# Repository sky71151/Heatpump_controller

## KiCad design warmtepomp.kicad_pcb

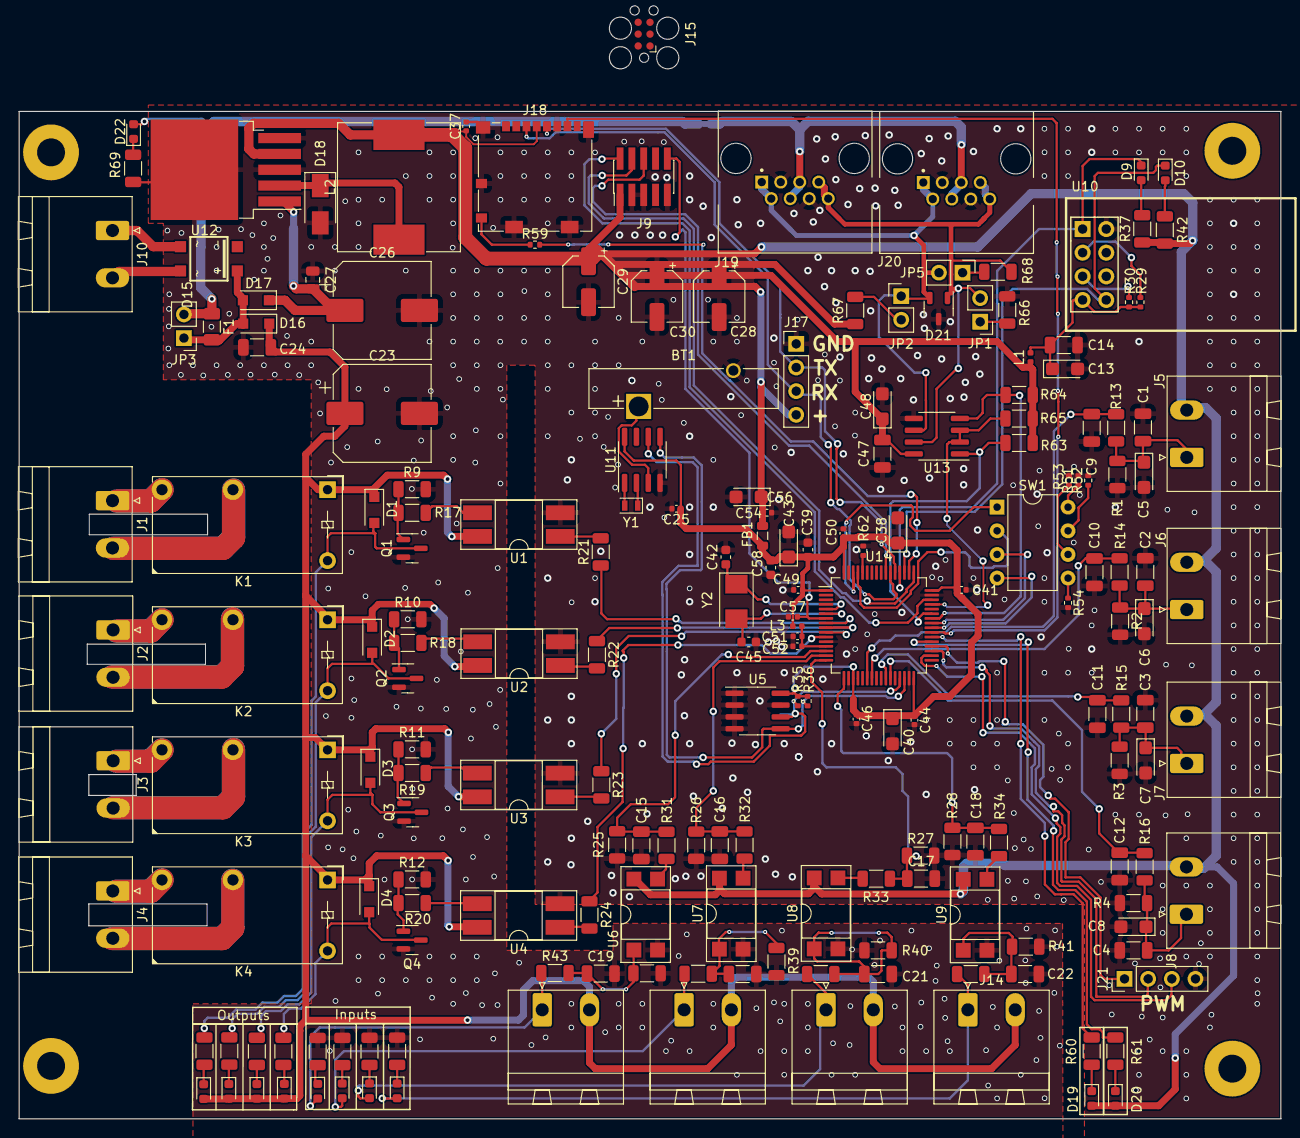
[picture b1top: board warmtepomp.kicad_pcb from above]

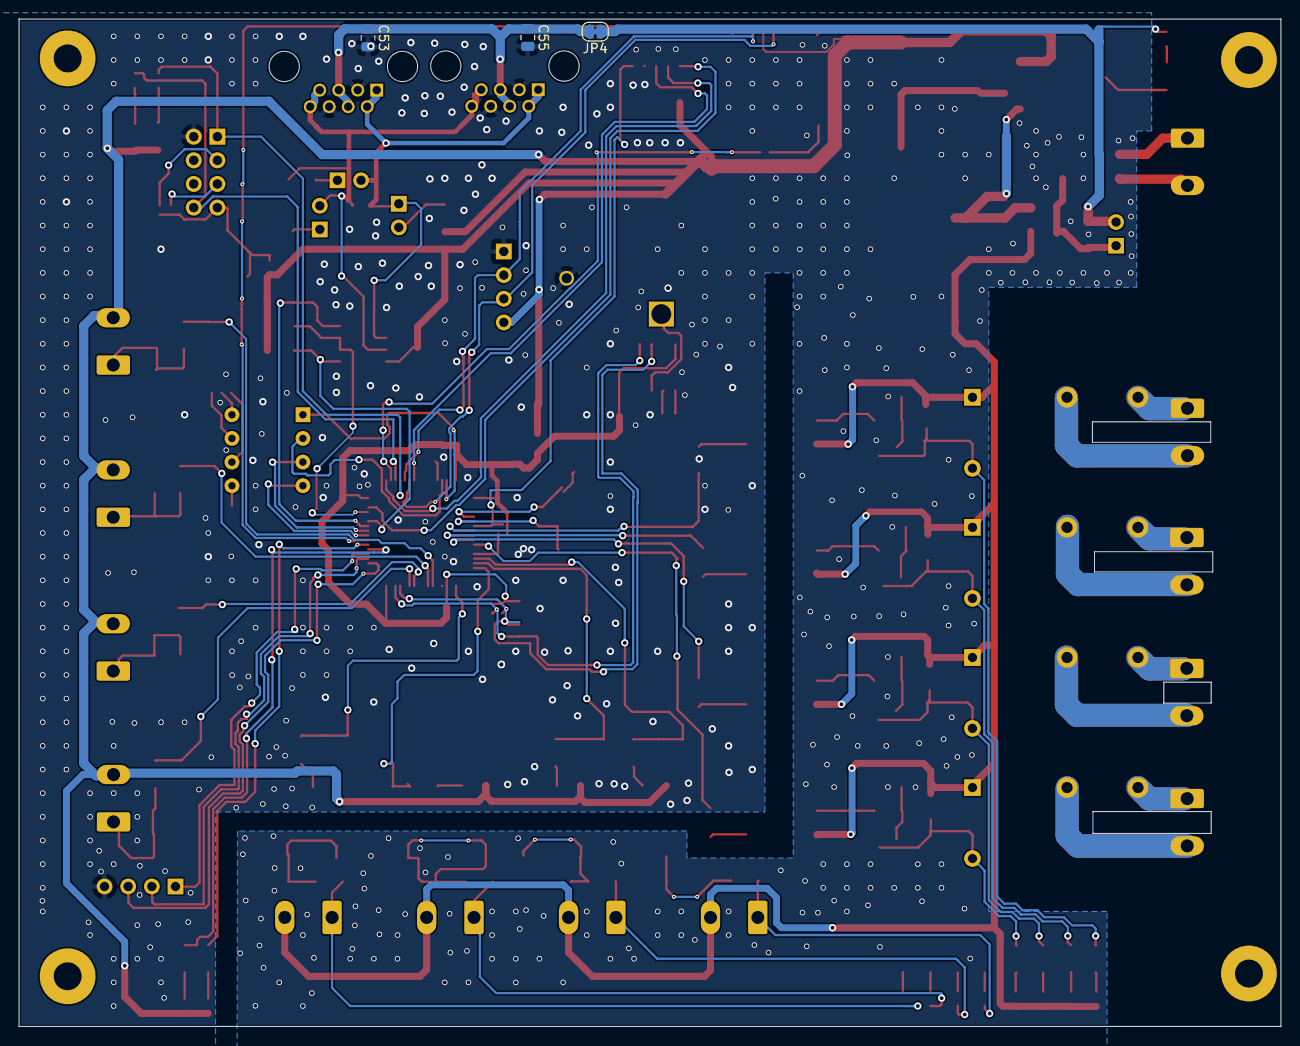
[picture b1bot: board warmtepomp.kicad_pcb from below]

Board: 2 copper layers, 135.5 x 108.2 mm, 199 parts (3 on the bottom side), 118 nets.

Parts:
BT1: Battery_Cell; Battery_Panasonic_CR2032-VS1N_Vertical_CircularHoles
C1, C2, C3, C4, C9, C10, C11, C12: 100nF; C_1206_3216Metric
C5, C6, C7, C8, C38, C40, C43, C54: 10µF; CP_EIA-3216-10_Kemet-I
C13: 4.7uf; CP_EIA-3216-10_Kemet-I
C14, C24: 4u7; C_1206_3216Metric
C15, C16, C17, C18: 10nF; C_1206_3216Metric
C19, C20, C21, C22, C47: 100nf; C_1206_3216Metric
C23, C26: 100µF 80V; CP_Elec_10x10
C25, C37, C41, C44, C46, C49, C50, C52, C56, C57: 100n; C_0402_1005Metric
C27, C53, C55: 100nF 100V; C_0805_2012Metric
C28, C29, C30: 100µF 10v; CP_Elec_5x5.4
C39: 4u7; C_0603_1608Metric
C42, C45: 30p; C_0603_1608Metric
C48: 10uF 16V; CP_EIA-3216-10_Kemet-I
C51: 1u; C_0402_1005Metric
C58: 10uF; C_0603_1608Metric
D1, D2, D3, D4, D16, D17: 1N4007; D_SOD-123F
D5, D6, D7, D8, D11, D12, D13, D14, D19, D20, D22: LED; LED_0603_1608Metric
D9: LED_RED; LED_0603_1608Metric
D10: LED_WIT; LED_0603_1608Metric
D15: D_Bridge_+-AA; SOIC-4
D18: SS32L-SS320L; D_SMA
D21: PSM712; SOT-23-3
F1: Polyfuse; Fuse_1206_3216Metric
FB1: FerriteBead_Small; L_0805_2012Metric
H1, H2, H3, H4: MountingHole; MountingHole_3mm_Pad
J1, J2, J3, J4: PhoenixContact_MSTBA_2,5_2-G-5,08_1x02_P5.08mm_Horizontal
J5, J6, J7, J8, J10, J11, J12, J13, J14: Screw_Terminal_01x02; PhoenixContact_MSTBA_2,5_2-G-5,08_1x02_P5.08mm_Horizontal
J9: Conn_02x05_Odd_Even; PinHeader_2x05_P1.27mm_Vertical_SMD
J15: Conn_ARM_SWD_TagConnect_TC2030; Tag-Connect_TC2030-IDC-FP_2x03_P1.27mm_Vertical
J17, J21: Conn_01x04; PinHeader_1x04_P2.54mm_Vertical
J18: Micro_SD_Card; microSD_HC_Molex_104031-0811
J19, J20: 1-406525-1; TE_1-406525-1
JP1, JP2, JP3, JP5: SolderJumper_2_Open; PinHeader_1x02_P2.54mm_Vertical
JP4: SolderJumper_2_Bridged; SolderJumper-2_P1.3mm_Bridged_RoundedPad1.0x1.5mm
K1, K2, K3, K4: RM50-xx21; Relay_SPST_Finder_32.21-x300
L1: 100µH; L_0402_1005Metric
L2: 100µH; L_Sunlord_MWSA12xxS
L3: 90mohm; L_0402_1005Metric
Q1, Q2, Q3, Q4: MMBTA42; SOT-23
R1, R2, R3, R4, R5, R6, R7, R8, R47, R48, R49, R50, R63, R64, R65, R66, R67: 10K; R_1206_3216Metric
R9, R10, R11, R12: 100K; R_1206_3216Metric
R13, R14, R15, R16, R21, R22, R23, R24: 300R; R_1206_3216Metric
R17, R18, R19, R20, R69: 2K; R_1206_3216Metric
R25, R26, R27, R28: 10k; R_1206_3216Metric
R29, R30, R51, R52, R53, R54, R62: 10k; R_0402_1005Metric
R31, R32, R33, R34: 100; R_1206_3216Metric
R35, R36: 4k7; R_0402_1005Metric
R37: 140; R_1206_3216Metric
R38, R39, R40, R41: 100k; R_1206_3216Metric
R42, R60, R61: 100R; R_1206_3216Metric
R43, R44, R45, R46: 2k; R_1206_3216Metric
R59: 100; R_0402_1005Metric
R68: 120; R_1206_3216Metric
SW1: SW_DIP_x04; DIP-8_W7.62mm
U1, U2, U3, U4: EL817; DIP-4_W8.89mm_SMDSocket_LongPads
U5: CAT24C256; SOIC-8_3.9x4.9mm_P1.27mm
U6, U7, U8, U9: EL817; DIP-4_W7.62mm_SMDSocket_SmallPads
U10: ESP-01v090; ESP-01
U11: DS1307Z+; SOIC-8_3.9x4.9mm_P1.27mm
U12: LM2576HVS-3.3; TO-263-5_TabPin3
U13: SN75176AP; SOIC-8_3.9x4.9mm_P1.27mm
U14: STM32F103RDTx; LQFP-64_10x10mm_P0.5mm
Y1: 32.768MHZ; Crystal_SMD_2012-2Pin_2.0x1.2mm
Y2: 8MHz; Crystal_SMD_5032-2Pin_5.0x3.2mm

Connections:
+3.3V: C28.1, C29.1, C30.1, C37.1, C47.1, C48.1, C54.1, C56.1, D19.2 (A), D20.2 (A), FB1.1, J5.2, J6.2, J7.2, J8.2, J9.1, J17.4, J18.4 (VDD), L1.2, L2.2, R37.1, R42.1, R63.2, R64.2, R65.2, R67.1, U6.4, U7.4, U8.4, U9.4, U12.4 (FB), U13.8 (VCC)
+3.3VA: C51.1, C52.1, L3.2, U14.13 (VDDA)
+24V: C23.1, C24.1, D1.1 (K), D2.1 (K), D3.1 (K), D4.1 (K), D5.2 (A), D6.2 (A), D7.2 (A), D8.2 (A), D16.1 (K), J11.2, J12.2, J13.2, J14.2, K1.A1, K2.A1, K3.A1, K4.A1, U1.4, U2.4, U3.4, U4.4
ADC0: C9.1, R13.2, U14.22 (PA6)
ADC1: C10.1, R14.2, U14.23 (PA7)
ADC2: C11.1, R15.2, U14.26 (PB0)
ADC3: C12.1, R16.2, U14.27 (PB1)
GND: BT1.2 (-), C1.2, C2.2, C3.2, C4.2, C5.2, C6.2, C7.2, C8.2, C9.2, C10.2, C11.2, C12.2, C13.2, C14.2, C15.2, C16.2, C17.2, C18.2, C19.2, C20.2, C21.2, C22.2, C23.2, C24.2, C25.2, C26.2, C27.2, C28.2, C29.2, C30.2, C38.2, C39.2, C40.2, C41.2, C42.2, C43.2, C44.2, C45.2, C46.2, C47.2, C48.2, C49.2, C50.2, C51.2, C52.2, C53.2, C54.2, C55.2, C56.2, C57.2, C58.2, D18.2 (A), D21.3 (common), J9.3, J9.5, J9.9, J17.1, J18.6 (VSS), J18.9 (DET_B), J18.11 (SHIELD), J19.3, J19.6, J20.3, J20.6, J21.4, Q1.2 (E), Q2.2 (E), Q3.2 (E), Q4.2 (E), R1.2, R2.2, R3.2, R4.2, R9.2, R10.2, R11.2, R12.2, R25.2, R26.2, R27.2, R28.2, R38.1, R39.1, R40.1, R41.1, R47.2, R48.2, R49.2, R50.2, R51.2, R52.2, R53.2, R54.2, R62.2, R66.2, R69.2, U1.2, U2.2, U3.2, U4.2, U5.1 (A0), U5.2 (A1), U5.3 (A2), U5.4 (GND), U5.7 (WP), U6.2, U7.2, U8.2, U9.2, U10.2 (GND), U11.4 (GND), U12.3 (GND), U12.5 (~ON/OFF), U13.5 (GND), U14.12 (VSSA), U14.18 (VSS), U14.31 (VSS), U14.47 (VSS), U14.63 (VSS)
GPIO0: C15.1, R25.1, R31.2, U14.14 (PA0)
GPIO1: C16.1, R26.1, R32.2, U14.15 (PA1)
GPIO2: C17.1, R27.1, R33.2, U14.16 (PA2)
GPIO3: C18.1, R28.1, R34.2, U14.17 (PA3)
NRST: C57.1, J9.10, U14.7 (NRST)
unnamed: BT1.1 (+), U11.3 (VBAT)
unnamed: C1.1, C5.1, J5.1, R1.1, R13.1
unnamed: C2.1, C6.1, J6.1, R2.1, R14.1
unnamed: C3.1, C7.1, J7.1, R3.1, R15.1
unnamed: C4.1, C8.1, J8.1, R4.1, R16.1
unnamed: C13.1, C14.1, L1.1, R29.2, R30.2, U10.7 (VCC)
unnamed: C19.1, R38.2, R43.2, U6.1
unnamed: C20.1, R39.2, R44.2, U7.1
unnamed: C21.1, R40.2, R45.2, U8.1
unnamed: C22.1, R41.2, R46.2, U9.1
unnamed: C26.1, C27.1, D17.1 (K), U12.1 (VIN)
unnamed: C42.1, U14.5 (PD0), Y2.1
unnamed: C45.1, U14.6 (PD1), Y2.2
unnamed: C53.1, C55.1, J19.4, J19.5, J20.4, J20.5, JP4.2 (B)
unnamed: D1.2 (A), K1.A2, Q1.3 (C), R5.2
unnamed: D2.2 (A), K2.A2, Q2.3 (C), R6.2
unnamed: D3.2 (A), K3.A2, Q3.3 (C), R7.2
unnamed: D4.2 (A), K4.A2, Q4.3 (C), R8.2
unnamed: D5.1 (K), R5.1
unnamed: D6.1 (K), R6.1
unnamed: D7.1 (K), R7.1
unnamed: D8.1 (K), R8.1
unnamed: D9.2 (A), R37.2
unnamed: D10.2 (A), R42.2
unnamed: D11.1 (K), R47.1
unnamed: D11.2 (A), J11.1, R43.1
unnamed: D12.1 (K), R48.1
unnamed: D12.2 (A), J12.1, R44.1
unnamed: D13.1 (K), R49.1
unnamed: D13.2 (A), J13.1, R45.1
unnamed: D14.1 (K), R50.1
unnamed: D14.2 (A), J14.1, R46.1
unnamed: D18.1 (K), L2.1, U12.2 (OUT)
unnamed: D19.1 (K), R60.1
unnamed: D20.1 (K), R61.1
unnamed: D21.1 (A1), J19.7, J19.8, J20.7, J20.8, JP1.2 (B), R68.2, U13.7 (B)
unnamed: D21.2 (A2), J19.1, J19.2, J20.1, J20.2, JP2.1 (A), JP5.2 (B), U13.6 (A)
unnamed: D22.1 (K), R69.1
unnamed: D22.2 (A), F1.1, JP3.2 (B), JP4.1 (A)
unnamed: J1.1, K1.14
unnamed: J1.2, K1.11
unnamed: J2.1, K2.14
unnamed: J2.2, K2.11
unnamed: J3.1, K3.14
unnamed: J3.2, K3.11
unnamed: J4.1, K4.14
unnamed: J4.2, K4.11
unnamed: J18.10 (DET_A), R59.1
unnamed: JP1.1 (A), R66.1
unnamed: JP2.2 (B), R67.2
unnamed: JP5.1 (A), R68.1
unnamed: Q1.1 (B), R9.1, R17.2
unnamed: Q2.1 (B), R10.1, R18.2
unnamed: Q3.1 (B), R11.1, R19.2
unnamed: Q4.1 (B), R12.1, R20.2
unnamed: R17.1, U1.3
unnamed: R18.1, U2.3
unnamed: R19.1, U3.3
unnamed: R20.1, U4.3
unnamed: R21.2, U1.1
unnamed: R22.2, U2.1
unnamed: R23.2, U3.1
unnamed: R24.2, U4.1
unnamed: R29.1, U10.3 (CH_PD)
unnamed: R30.1, U10.5 (RST)
unnamed: R31.1, U6.3
unnamed: R32.1, U7.3
unnamed: R33.1, U8.3
unnamed: R34.1, U9.3
unnamed: R51.1, SW1.8
unnamed: R52.1, SW1.7
unnamed: R53.1, SW1.6
unnamed: R54.1, SW1.5
unnamed: R60.2, U14.38 (PC7)
unnamed: R61.2, U14.37 (PC6)
unnamed: R62.1, U14.60 (BOOT0)
unnamed: U11.1 (X1), Y1.2
unnamed: U11.2 (X2), Y1.1
PA8: SW1.3, U14.41 (PA8)
PB8: SW1.2, U14.61 (PB8)
PB9: SW1.1, U14.62 (PB9)
PB13: J21.3, U14.34 (PB13)
PB14: J21.2, U14.35 (PB14)
PB15: J21.1, U14.36 (PB15)
PC9: SW1.4, U14.40 (PC9)
PC_RX: J17.3, J18.3 (CMD), U14.54 (PD2)
PC_TX: J17.2, J18.5 (CLK), U14.53 (PC12)
RELAY0: R21.1, U14.8 (PC0)
RELAY1: R22.1, U14.9 (PC1)
RELAY2: R23.1, U14.10 (PC2)
RELAY3: R24.1, U14.11 (PC3)
SCL: R35.2, U5.6 (SCL), U11.6 (SCL), U14.29 (PB10)
SDA: R36.2, U5.5 (SDA), U11.5 (SDA), U14.30 (PB11)
SDIO_DO: J18.7 (DAT0), U14.39 (PC8)
SD_CARD_DETECTION: R59.2, U14.50 (PA15)
STM32_RS485: R65.1, U13.2 (~RE), U13.3 (DE), U14.45 (PA12)
STM32_RX_4: D9.1 (K), U10.1 (UTXD), U14.52 (PC11)
STM32_RX_5: R63.1, U13.1 (R), U14.43 (PA10)
STM32_TX_4: D10.1 (K), U10.8 (URXD), U14.51 (PC10)
STM32_TX_5: R64.1, U13.4 (D), U14.42 (PA9)
SWCLK: J9.4, U14.49 (PA14)
SWDIO: J9.2, U14.46 (PA13)
SWO: J9.6, U14.55 (PB3)
VDC: D16.2 (A), D17.2 (A), F1.2, JP3.1 (A)
VDD: C25.1, C38.1, C39.1, C40.1, C41.1, C43.1, C44.1, C46.1, C49.1, C50.1, C58.1, FB1.2, L3.1, R35.1, R36.1, U5.8 (VCC), U11.8 (VCC), U14.1 (VBAT), U14.19 (VDD), U14.32 (VDD), U14.48 (VDD), U14.64 (VDD)
